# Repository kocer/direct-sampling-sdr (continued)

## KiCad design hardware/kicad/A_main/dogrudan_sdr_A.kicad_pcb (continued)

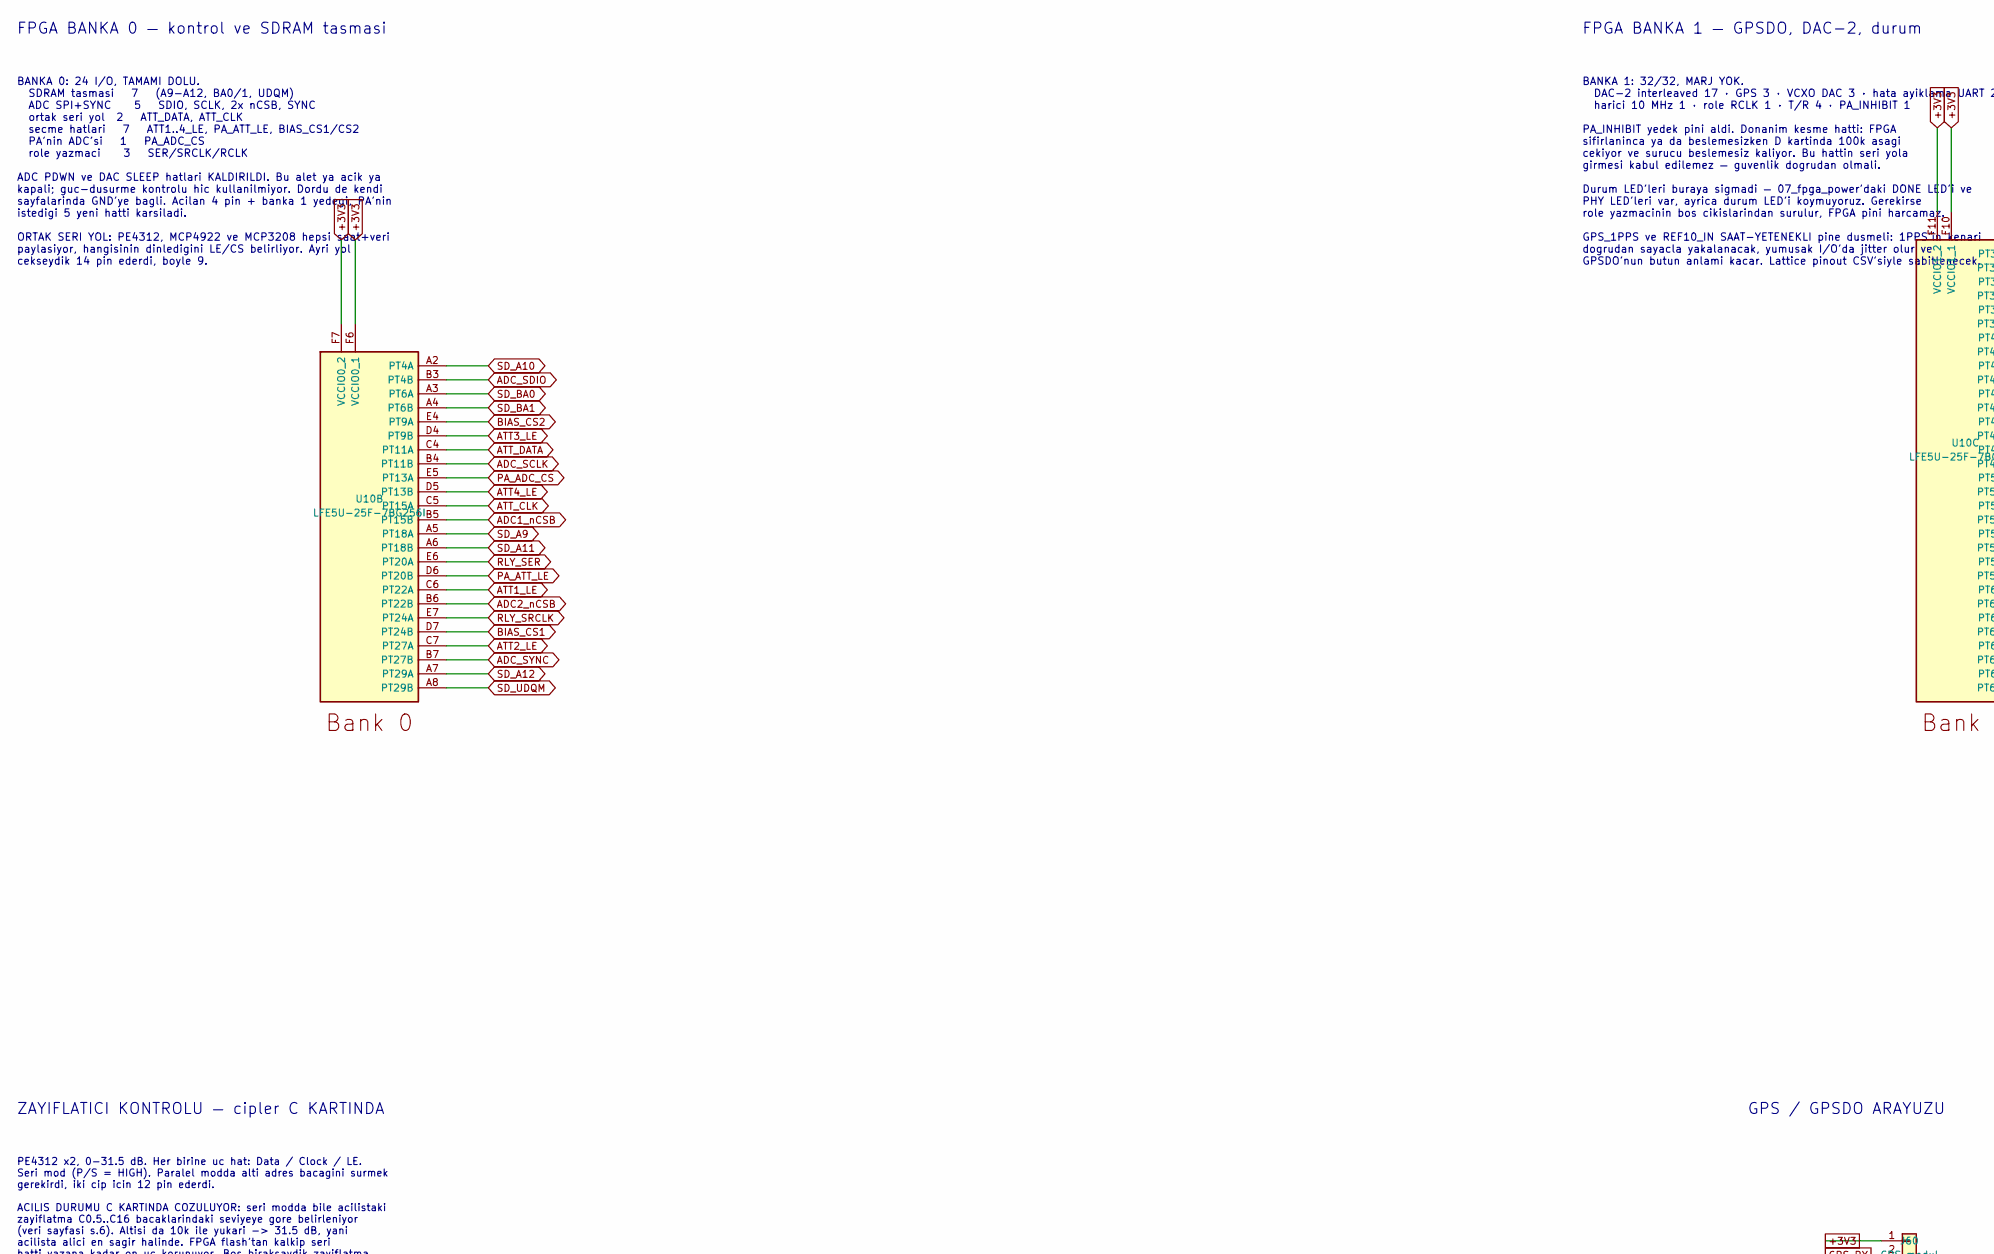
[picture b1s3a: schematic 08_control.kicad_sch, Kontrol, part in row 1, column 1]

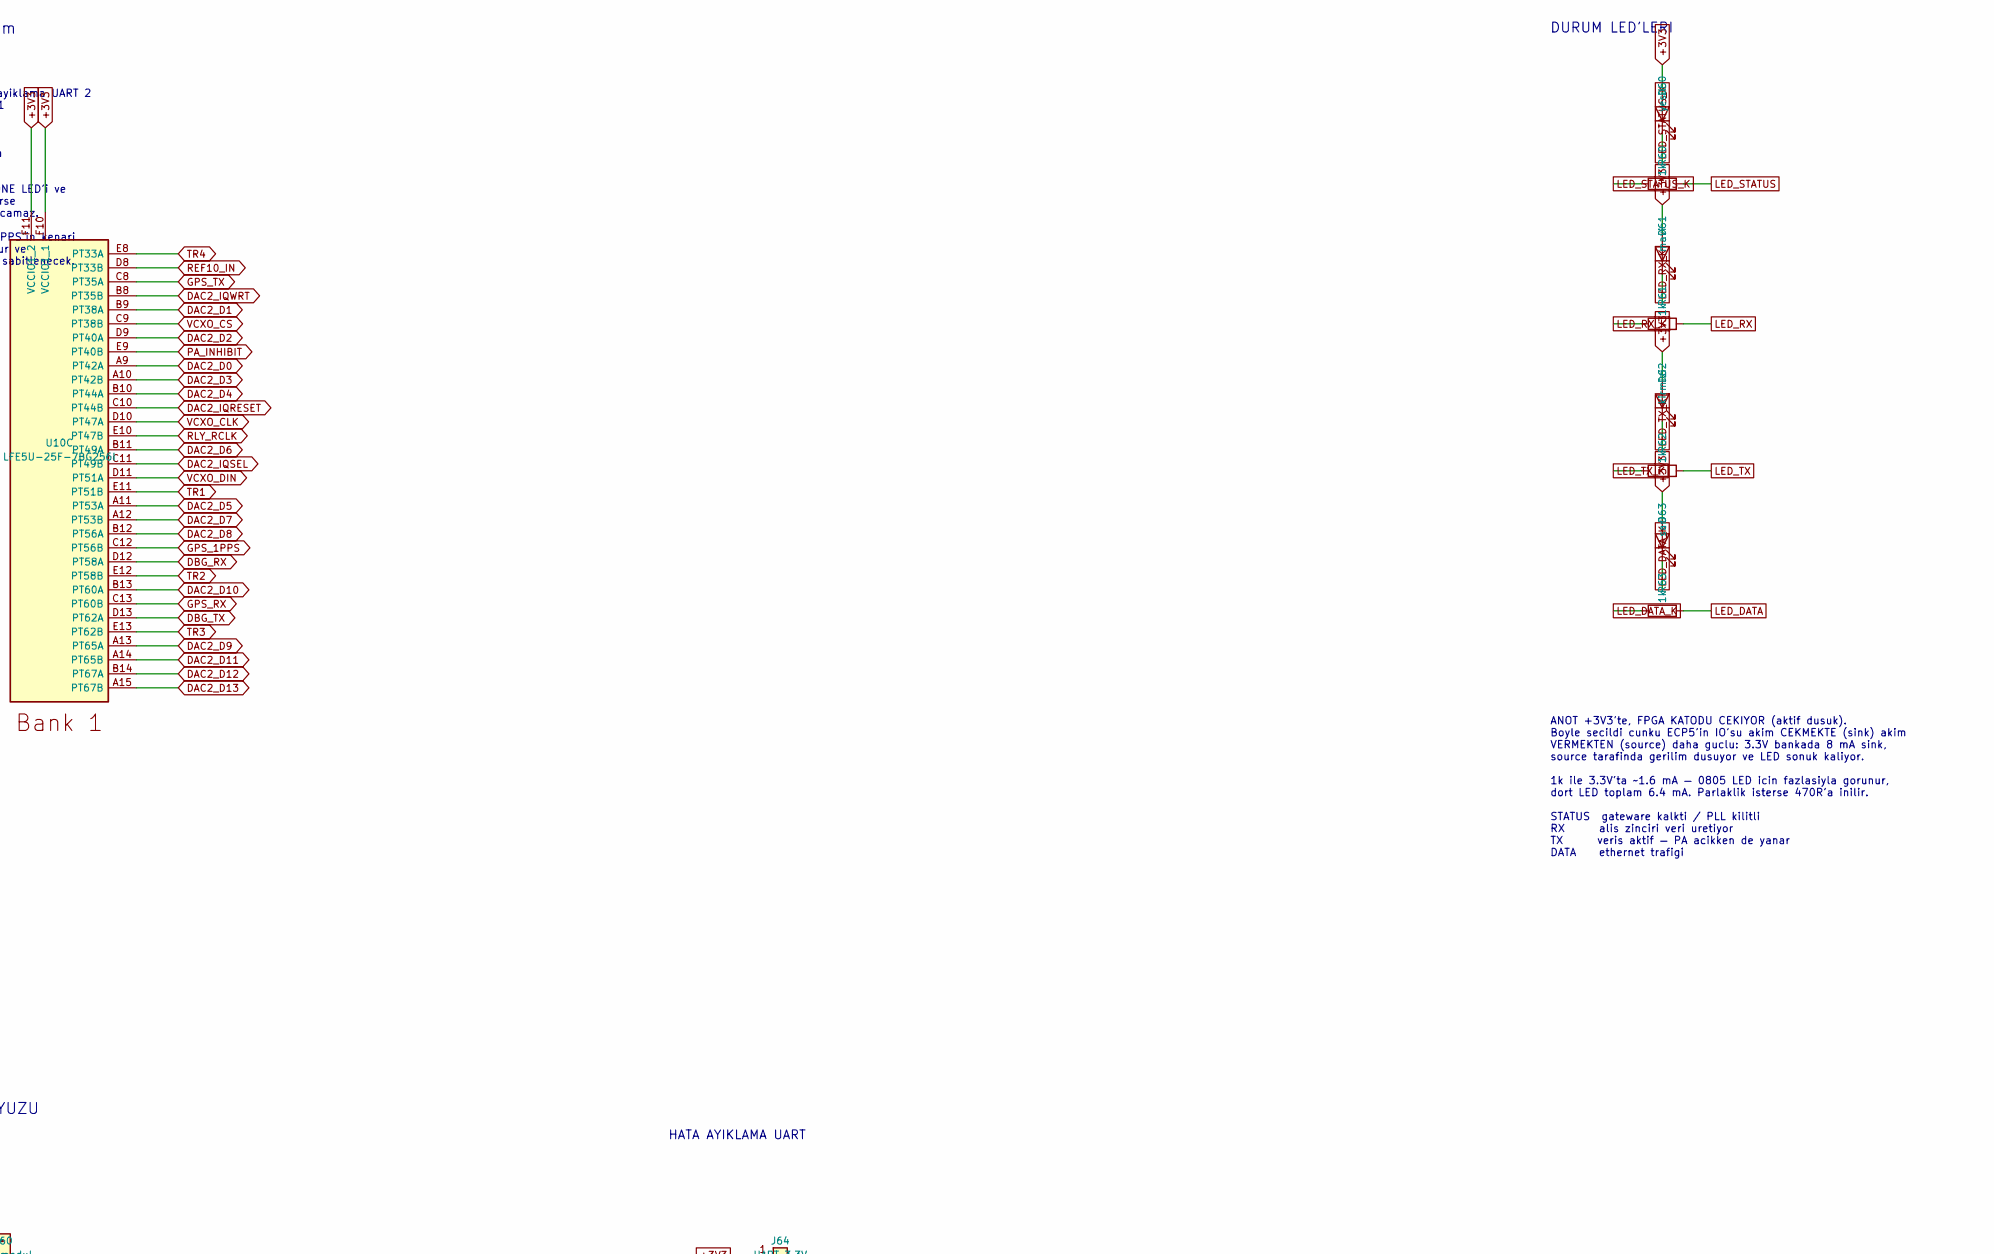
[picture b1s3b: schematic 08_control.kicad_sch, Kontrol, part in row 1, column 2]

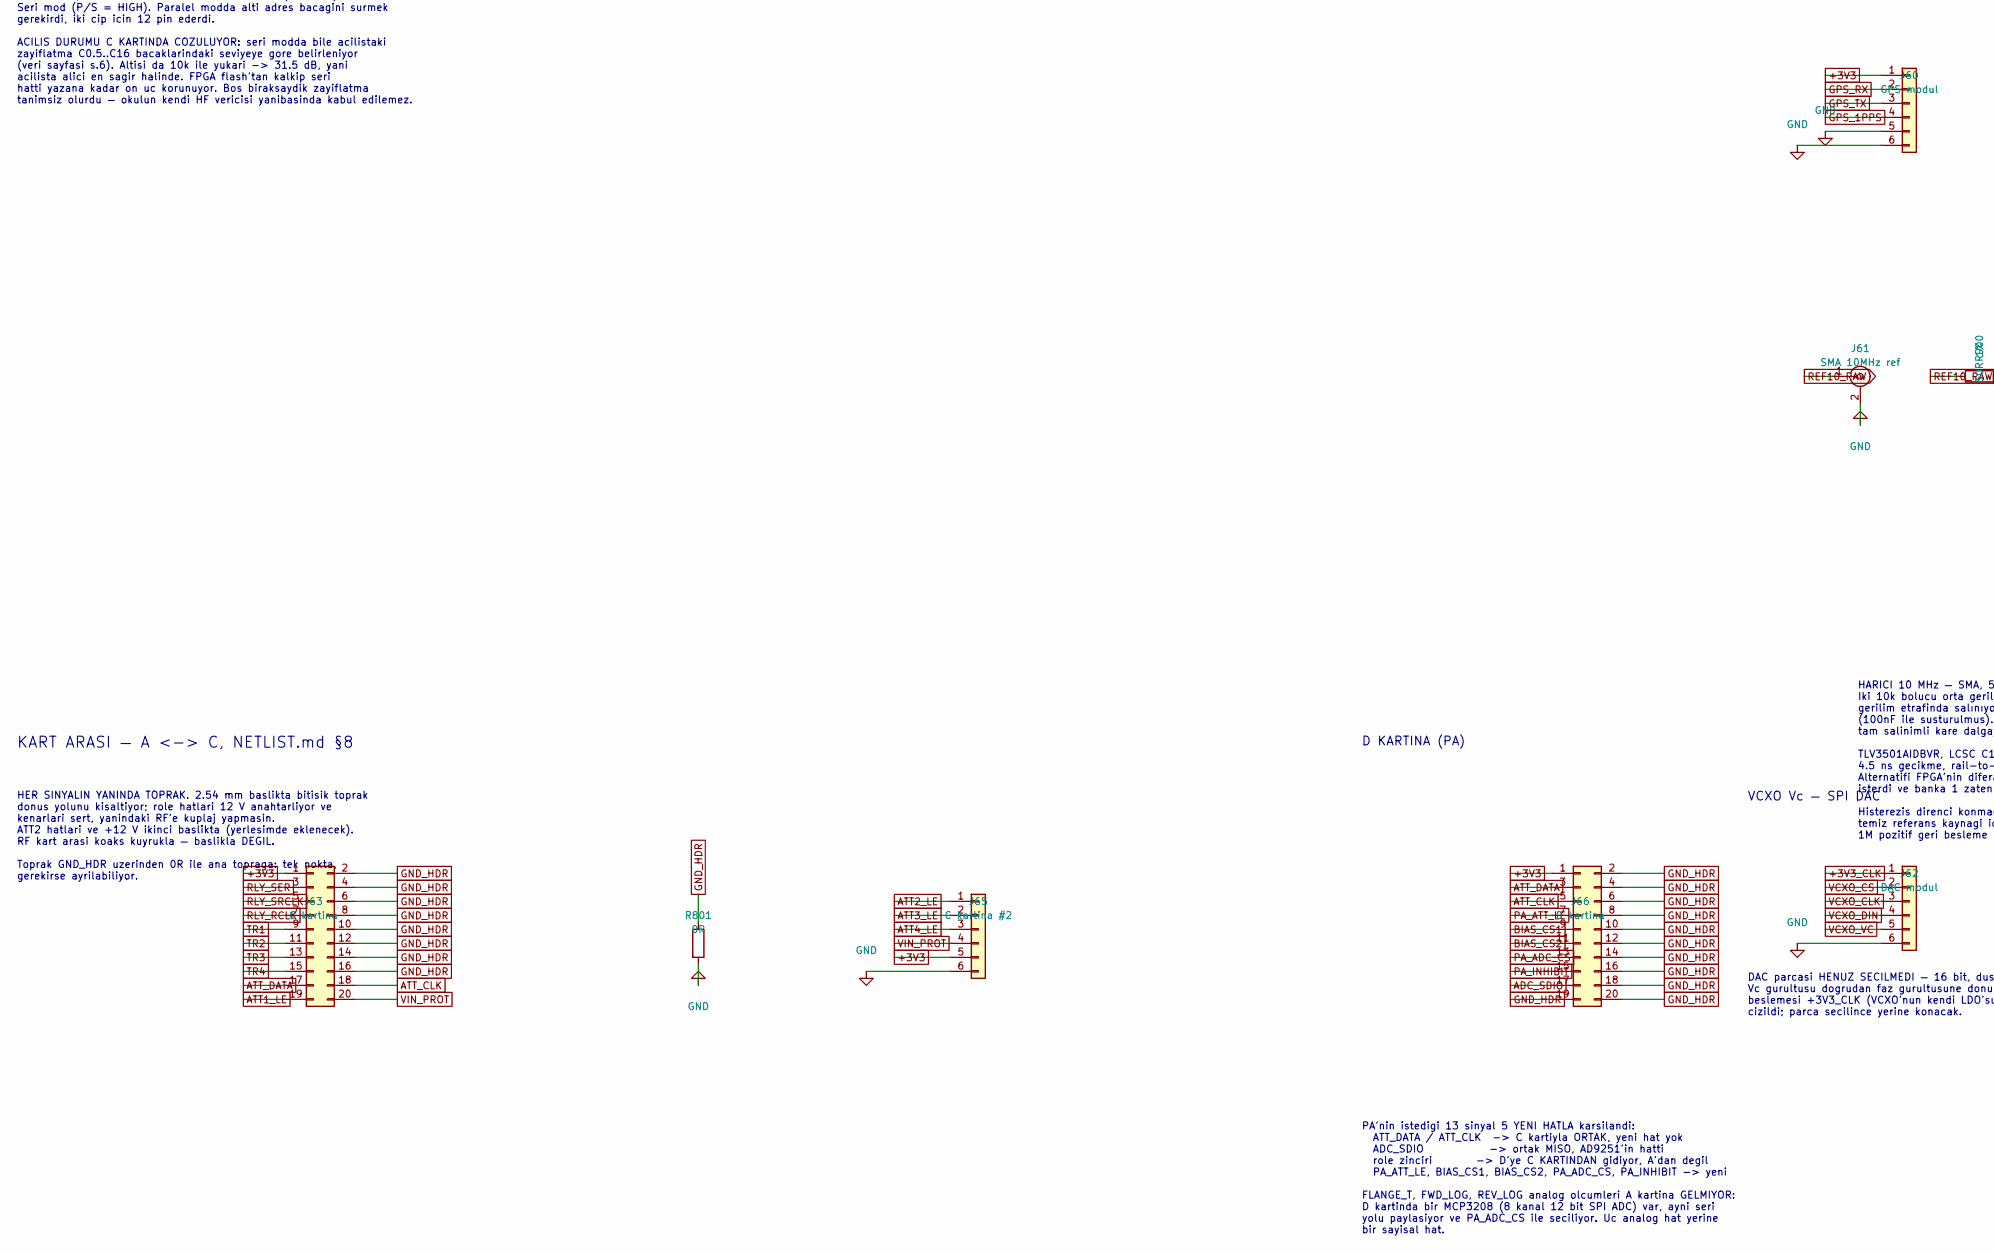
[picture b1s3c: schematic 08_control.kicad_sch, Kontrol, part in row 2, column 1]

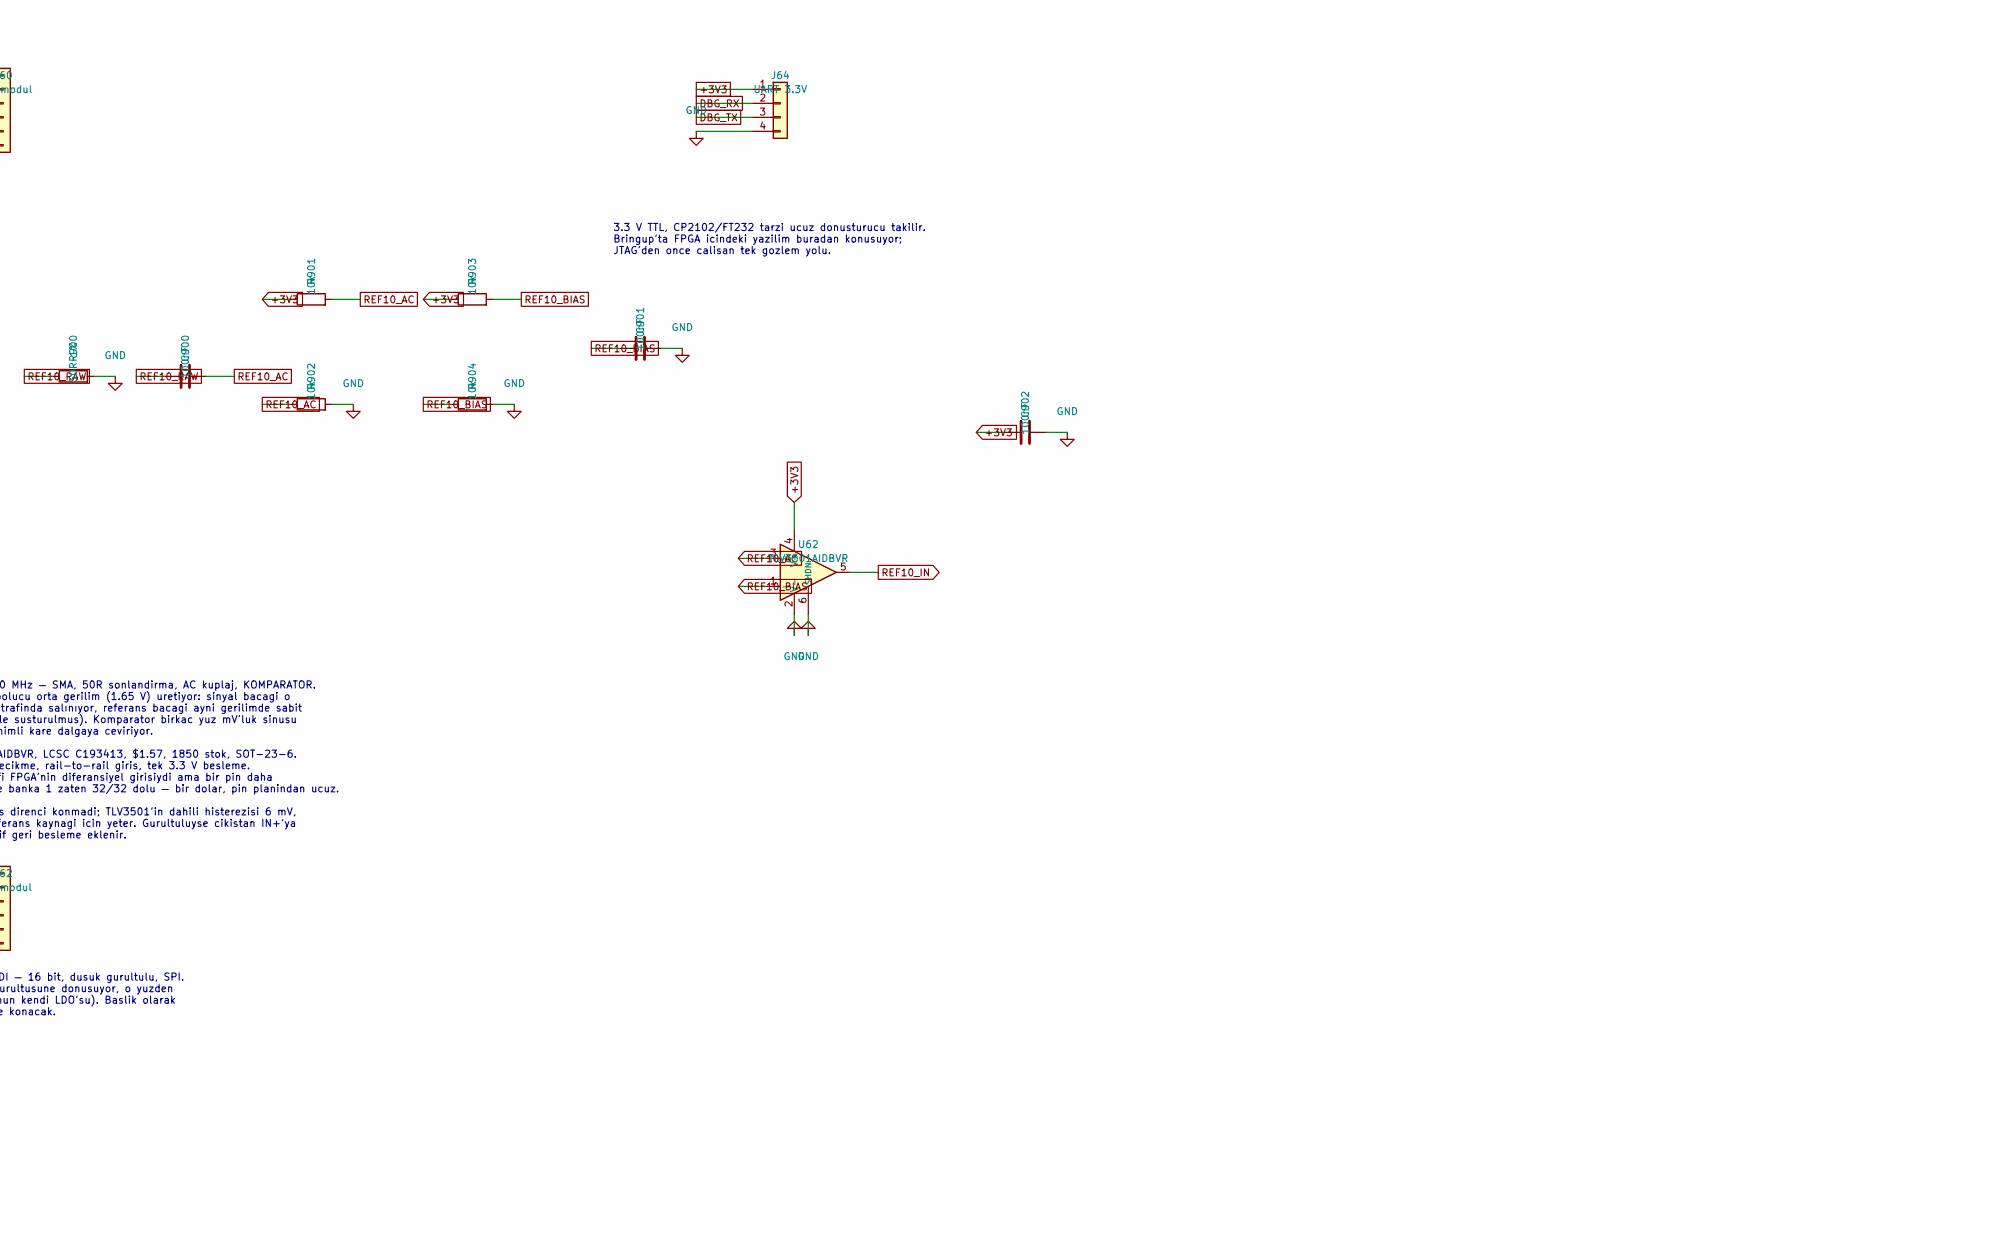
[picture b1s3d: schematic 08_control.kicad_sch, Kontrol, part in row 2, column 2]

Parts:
C900, C901, C902: 100nF; C_0603_1608Metric
D60: yesil; LED_0805_2012Metric
D61: mavi; LED_0805_2012Metric
D62: kirmizi; LED_0805_2012Metric
D63: sari; LED_0805_2012Metric
J60: GPS modul; PinHeader_1x06_P2.54mm_Vertical
J61: SMA 10MHz ref; SMA_Amphenol_132289_EdgeMount
J62: DAC modul; PinHeader_1x06_P2.54mm_Vertical
J63: C kartina; PinHeader_2x10_P2.54mm_Vertical
J64: UART 3.3V; PinHeader_1x04_P2.54mm_Vertical
J65: C kartina #2; PinHeader_1x06_P2.54mm_Vertical
J66: D kartina; PinHeader_2x10_P2.54mm_Vertical
R60, R61, R62, R63: 1k; R_0603_1608Metric
R801: 0R; R_0603_1608Metric
R900: 50R 1%; R_0603_1608Metric
R901, R902, R903, R904: 10k; R_0603_1608Metric
U10: LFE5U-25F-7BG256I; BGA-256_14.0x14.0mm_Layout16x16_P0.8mm_Ball0.45mm_Pad0.32mm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
U62: TLV3501AIDBVR; SOT-23-6

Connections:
ADC1_nCSB: U10.B5 (PT15B); also elsewhere on the board
ADC2_nCSB: U10.B6 (PT22B); also elsewhere on the board
ADC_SCLK: U10.B4 (PT11B); also elsewhere on the board
ADC_SDIO: J66.17, U10.B3 (PT4B); also elsewhere on the board
ADC_SYNC: U10.B7 (PT27B); also elsewhere on the board
ATT1_LE: J63.19, U10.C6 (PT22A)
ATT2_LE: J65.1, U10.C7 (PT27A)
ATT3_LE: J65.2, U10.D4 (PT9B)
ATT4_LE: J65.3, U10.D5 (PT13B)
ATT_CLK: J63.18, J66.5, U10.C5 (PT15A)
ATT_DATA: J63.17, J66.3, U10.C4 (PT11A)
BIAS_CS1: J66.9, U10.D7 (PT24B)
BIAS_CS2: J66.11, U10.E4 (PT9A)
DAC2_D0: U10.A9 (PT42A); also elsewhere on the board
DAC2_D1: U10.B9 (PT38A); also elsewhere on the board
DAC2_D2: U10.D9 (PT40A); also elsewhere on the board
DAC2_D3: U10.A10 (PT42B); also elsewhere on the board
DAC2_D4: U10.B10 (PT44A); also elsewhere on the board
DAC2_D5: U10.A11 (PT53A); also elsewhere on the board
DAC2_D6: U10.B11 (PT49A); also elsewhere on the board
DAC2_D7: U10.A12 (PT53B); also elsewhere on the board
DAC2_D8: U10.B12 (PT56A); also elsewhere on the board
DAC2_D9: U10.A13 (PT65A); also elsewhere on the board
DAC2_D10: U10.B13 (PT60A); also elsewhere on the board
DAC2_D11: U10.A14 (PT65B); also elsewhere on the board
DAC2_D12: U10.B14 (PT67A); also elsewhere on the board
DAC2_D13: U10.A15 (PT67B); also elsewhere on the board
DAC2_IQRESET: U10.C10 (PT44B); also elsewhere on the board
DAC2_IQSEL: U10.C11 (PT49B); also elsewhere on the board
DAC2_IQWRT: U10.B8 (PT35B); also elsewhere on the board
DBG_RX: J64.2, U10.D12 (PT58A)
DBG_TX: J64.3, U10.D13 (PT62A)
GND_HDR: J63.2, J63.4, J63.6, J63.8, J63.10, J63.12, J63.14, J63.16, J66.2, J66.4, J66.6, J66.8, J66.10, J66.12, J66.14, J66.16, J66.18, J66.19, J66.20, R801.1
GPS_1PPS: J60.4, U10.C12 (PT56B)
GPS_RX: J60.2, U10.C13 (PT60B)
GPS_TX: J60.3, U10.C8 (PT35A)
LED_DATA: R63.2; also elsewhere on the board
LED_DATA_K: D63.1 (K), R63.1
LED_RX: R61.2; also elsewhere on the board
LED_RX_K: D61.1 (K), R61.1
LED_STATUS: R60.2; also elsewhere on the board
LED_STATUS_K: D60.1 (K), R60.1
LED_TX: R62.2; also elsewhere on the board
LED_TX_K: D62.1 (K), R62.1
PA_ADC_CS: J66.13, U10.E5 (PT13A)
PA_ATT_LE: J66.7, U10.D6 (PT20B)
PA_INHIBIT: J66.15, U10.E9 (PT40B)
REF10_AC: C900.2, R901.2, R902.1, U62.3 (+)
REF10_BIAS: C901.1, R903.2, R904.1, U62.1 (-)
REF10_IN: U10.D8 (PT33B), U62.5; also elsewhere on the board
REF10_RAW: C900.1, J61.1 (In), R900.1
RLY_RCLK: J63.7, U10.E10 (PT47B)
RLY_SER: J63.3, U10.E6 (PT20A)
RLY_SRCLK: J63.5, U10.E7 (PT24A)
SD_A9: U10.A5 (PT18A); also elsewhere on the board
SD_A10: U10.A2 (PT4A); also elsewhere on the board
SD_A11: U10.A6 (PT18B); also elsewhere on the board
SD_A12: U10.A7 (PT29A); also elsewhere on the board
SD_BA0: U10.A3 (PT6A); also elsewhere on the board
SD_BA1: U10.A4 (PT6B); also elsewhere on the board
SD_UDQM: U10.A8 (PT29B); also elsewhere on the board
TR1: J63.9, U10.E11 (PT51B)
TR2: J63.11, U10.E12 (PT58B)
TR3: J63.13, U10.E13 (PT62B)
TR4: J63.15, U10.E8 (PT33A)
VCXO_CLK: J62.3, U10.D10 (PT47A)
VCXO_CS: J62.2, U10.C9 (PT38B)
VCXO_DIN: J62.4, U10.D11 (PT51A)
VCXO_VC: J62.5; also elsewhere on the board

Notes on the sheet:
FPGA BANKA 1 — GPSDO, DAC-2, durum
KART ARASI — A <-> C, NETLIST.md §8
FPGA BANKA 0 — kontrol ve SDRAM tasmasi
ANOT +3V3'te, FPGA KATODU CEKIYOR (aktif dusuk). Boyle secildi cunku ECP5'in IO'su akim CEKMEKTE (sink) akim VERMEKTEN (source) daha guclu: 3.3V bankada 8 mA sink, source tarafinda gerilim dusuyor ve LED sonuk kaliyor. 1k ile 3.3V'ta ~1.6 mA — 0805 LED icin fazlasiyla gorunur, dort LED toplam 6.4 m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
GPS / GPSDO ARAYUZU
HER SINYALIN YANINDA TOPRAK. 2.54 mm baslikta bitisik toprak donus yolunu kisaltiyor; role hatlari 12 V anahtarliyor ve kenarlari sert, yanindaki RF'e kuplaj yapmasin. ATT2 hatlari ve +12 V ikinci baslikta (yerlesimde eklenecek). RF kart arasi koaks kuyrukla — baslikla DEGIL. Toprak GND_HDR uzerind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
BANKA 0: 24 I/O, TAMAMI DOLU. SDRAM tasmasi 7 (A9-A12, BA0/1, UDQM) ADC SPI+SYNC 5 SDIO, SCLK, 2x nCSB, SYNC ortak seri yol 2 ATT_DATA, ATT_CLK secme hatlari 7 ATT1..4_LE, PA_ATT_LE, BIAS_CS1/CS2 PA'nin ADC'si 1 PA_ADC_CS role yazmaci 3 SER/SRCLK/RCLK ADC PDWN ve DAC SLEEP hatlari KALDIRILDI. Bu al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
3.3 V TTL, CP2102/FT232 tarzi ucuz donusturucu takilir. Bringup'ta FPGA icindeki yazilim buradan konusuyor; JTAG'den once calisan tek gozlem yolu.
HATA AYIKLAMA UART
PE4312 x2, 0-31.5 dB. Her birine uc hat: Data / Clock / LE. Seri mod (P/S = HIGH). Paralel modda alti adres bacagini surmek gerekirdi, iki cip icin 12 pin ederdi. ACILIS DURUMU C KARTINDA COZULUYOR: seri modda bile acilistaki zayiflatma C0.5..C16 bacaklarindaki seviyeye gore belirleniyor (veri sayf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
HARICI 10 MHz — SMA, 50R sonlandirma, AC kuplaj, KOMPARATOR. Iki 10k bolucu orta gerilim (1.65 V) uretiyor: sinyal bacagi o gerilim etrafinda salınıyor, referans bacagi ayni gerilimde sabit (100nF ile susturulmus). Komparator birkac yuz mV'luk sinusu tam salinimli kare dalgaya ceviriyor. TLV3501AID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
D KARTINA (PA)
ZAYIFLATICI KONTROLU — cipler C KARTINDA
BANKA 1: 32/32, MARJ YOK. DAC-2 interleaved 17 · GPS 3 · VCXO DAC 3 · hata ayiklama UART 2 harici 10 MHz 1 · role RCLK 1 · T/R 4 · PA_INHIBIT 1 PA_INHIBIT yedek pini aldi. Donanim kesme hatti: FPGA sifirlaninca ya da beslemesizken D kartinda 100k asagi cekiyor ve surucu beslemesiz kaliyor. Bu hatti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
PA'nin istedigi 13 sinyal 5 YENI HATLA karsilandi: ATT_DATA / ATT_CLK -> C kartiyla ORTAK, yeni hat yok ADC_SDIO -> ortak MISO, AD9251'in hatti role zinciri -> D'ye C KARTINDAN gidiyor, A'dan degil PA_ATT_LE, BIAS_CS1, BIAS_CS2, PA_ADC_CS, PA_INHIBIT -> yeni FLANGE_T, FWD_LOG, REV_LOG analog olcuml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
DAC parcasi HENUZ SECILMEDI — 16 bit, dusuk gurultulu, SPI. Vc gurultusu dogrudan faz gurultusune donusuyor, o yuzden beslemesi +3V3_CLK (VCXO'nun kendi LDO'su). Baslik olarak cizildi; parca secilince yerine konacak.
VCXO Vc — SPI DAC
DURUM LED'LERI

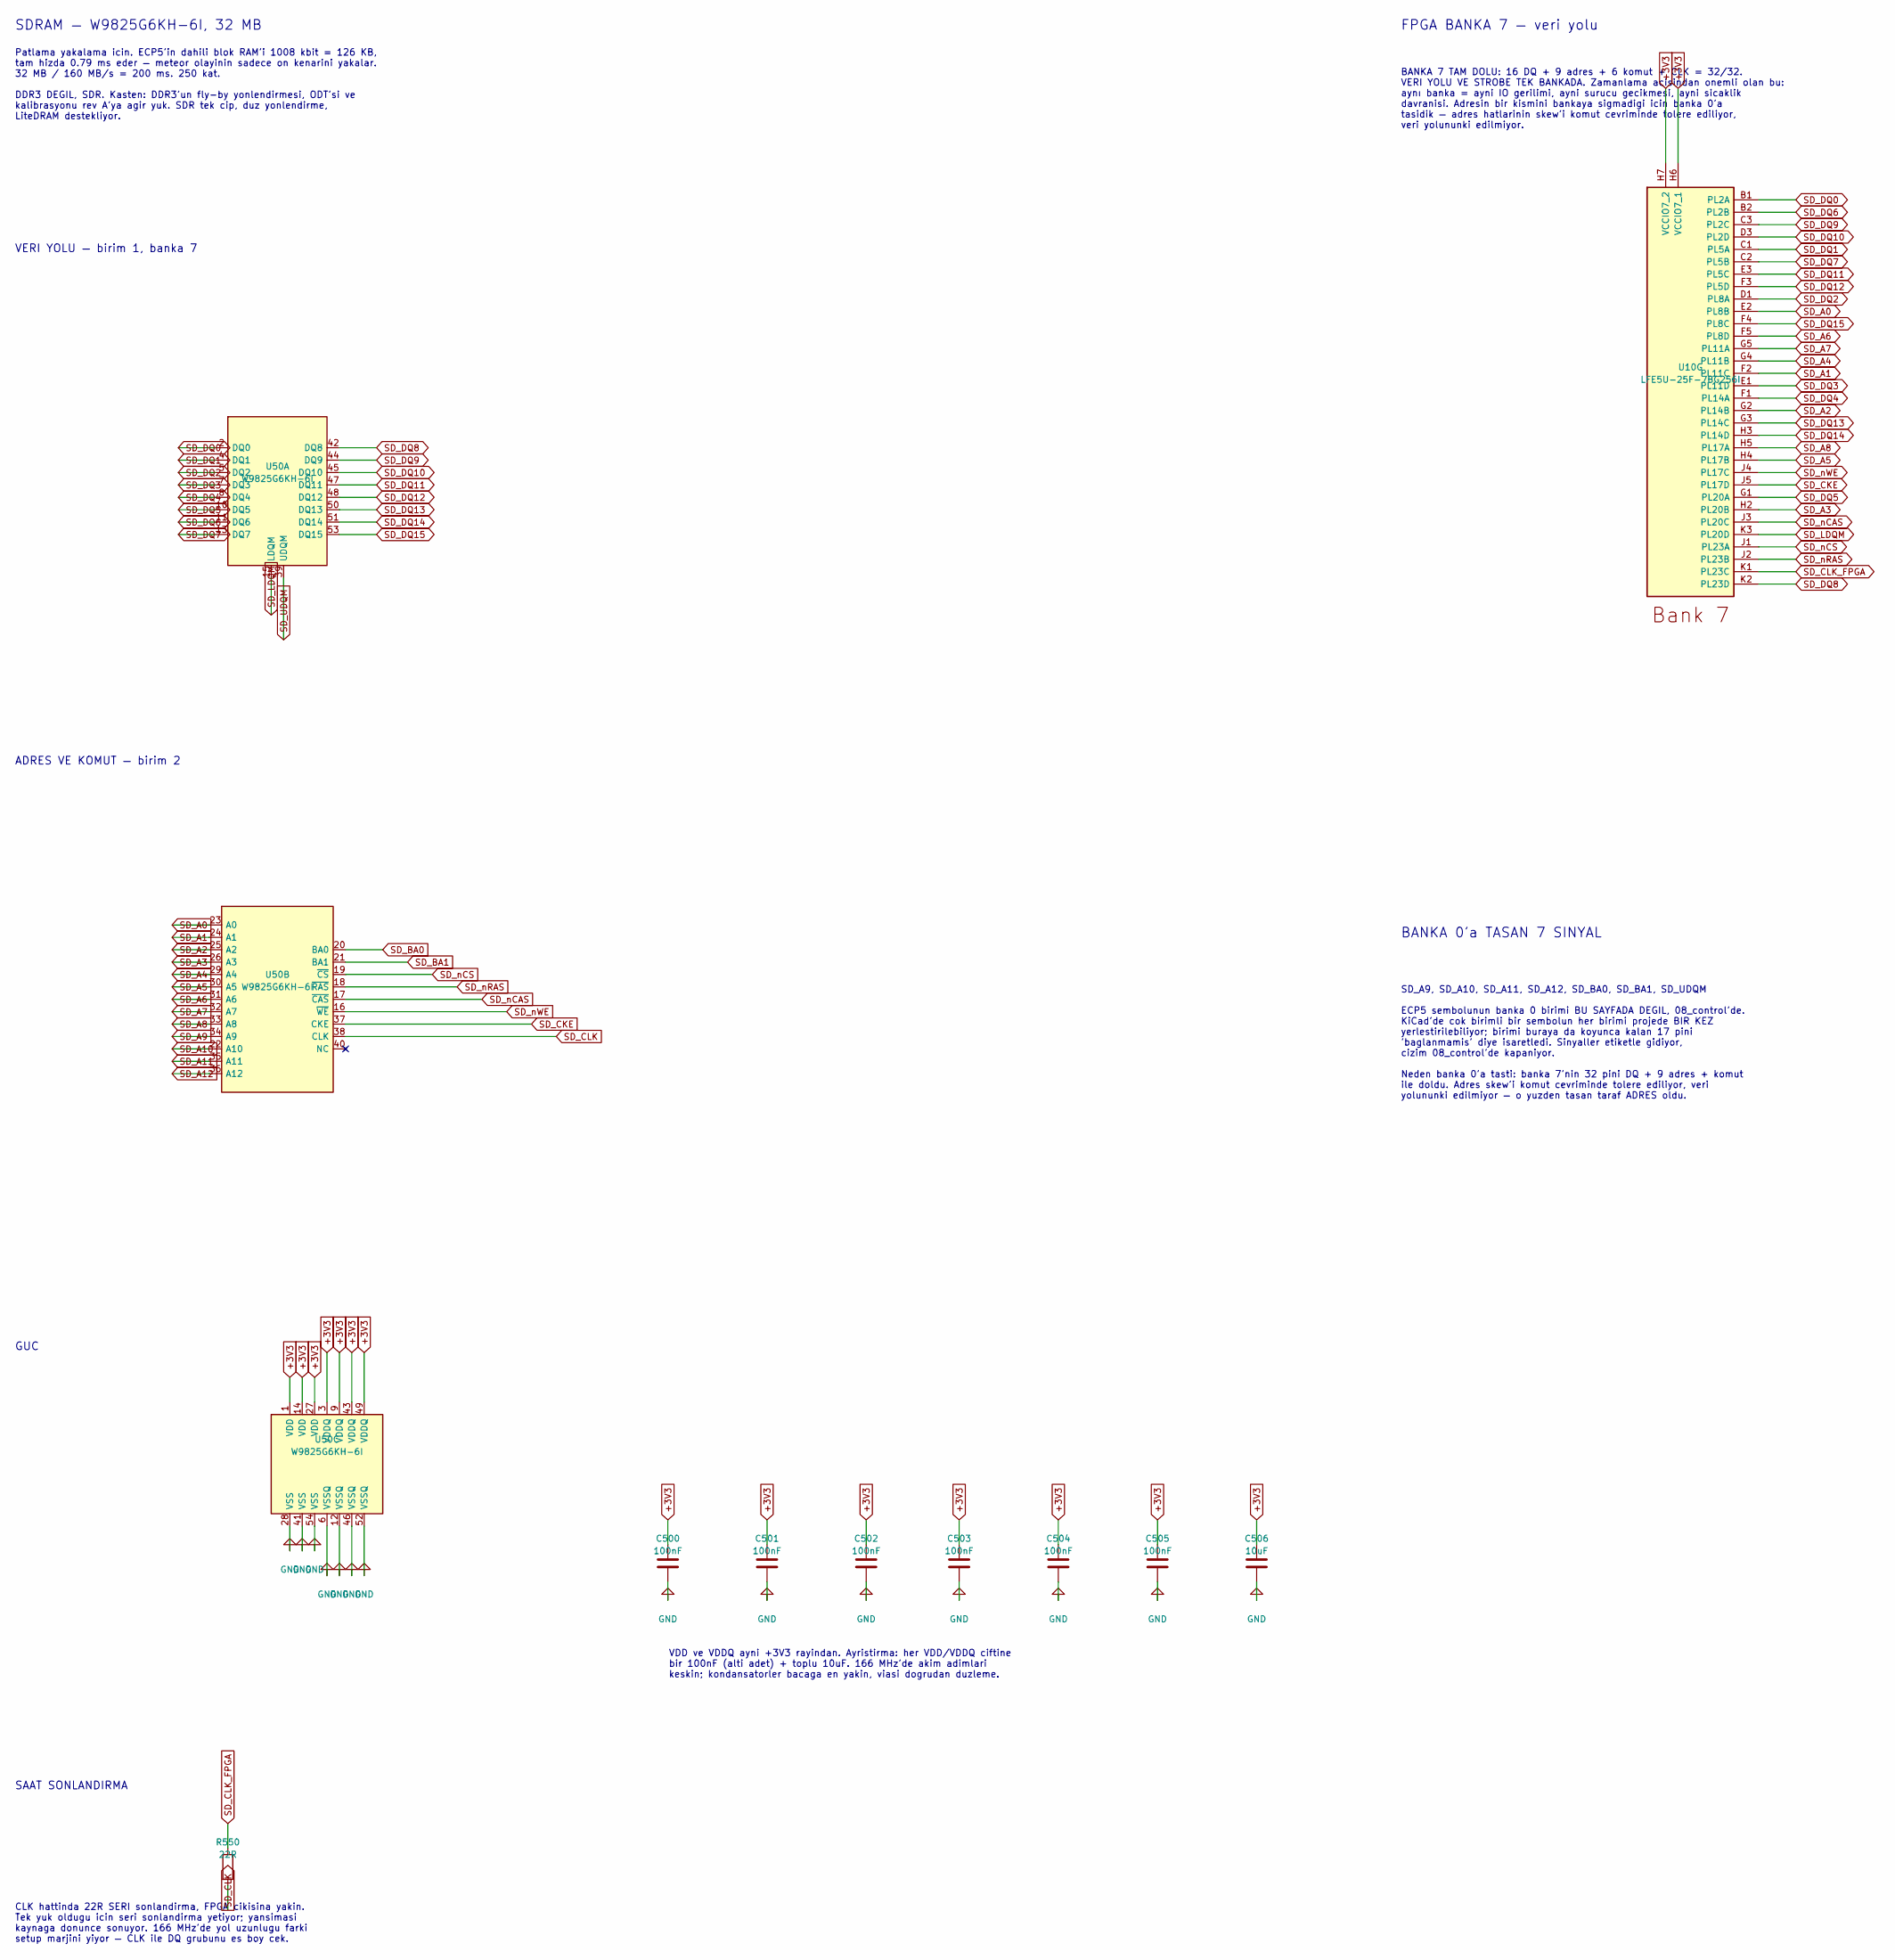
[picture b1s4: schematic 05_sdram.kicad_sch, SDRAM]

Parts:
C500, C501, C502, C503, C504, C505: 100nF; C_0603_1608Metric
C506: 10uF; C_0603_1608Metric
R550: 22R; R_0603_1608Metric
U10: LFE5U-25F-7BG256I; BGA-256_14.0x14.0mm_Layout16x16_P0.8mm_Ball0.45mm_Pad0.32mm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
U50: W9825G6KH-6I; TSOP-II-54_22.2x10.16mm_P0.8mm

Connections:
SD_A0: U10.E2 (PL8B), U50.23 (A0)
SD_A1: U10.F2 (PL11C), U50.24 (A1)
SD_A2: U10.G2 (PL14B), U50.25 (A2)
SD_A3: U10.H2 (PL20B), U50.26 (A3)
SD_A4: U10.G4 (PL11B), U50.29 (A4)
SD_A5: U10.H4 (PL17B), U50.30 (A5)
SD_A6: U10.F5 (PL8D), U50.31 (A6)
SD_A7: U10.G5 (PL11A), U50.32 (A7)
SD_A8: U10.H5 (PL17A), U50.33 (A8)
SD_A9: U50.34 (A9); also elsewhere on the board
SD_A10: U50.22 (A10); also elsewhere on the board
SD_A11: U50.35 (A11); also elsewhere on the board
SD_A12: U50.36 (A12); also elsewhere on the board
SD_BA0: U50.20 (BA0); also elsewhere on the board
SD_BA1: U50.21 (BA1); also elsewhere on the board
SD_CKE: U10.J5 (PL17D), U50.37 (CKE)
SD_CLK: R550.2, U50.38 (CLK)
SD_CLK_FPGA: R550.1, U10.K1 (PL23C)
SD_DQ0: U10.B1 (PL2A), U50.2 (DQ0)
SD_DQ1: U10.C1 (PL5A), U50.4 (DQ1)
SD_DQ2: U10.D1 (PL8A), U50.5 (DQ2)
SD_DQ3: U10.E1 (PL11D), U50.7 (DQ3)
SD_DQ4: U10.F1 (PL14A), U50.8 (DQ4)
SD_DQ5: U10.G1 (PL20A), U50.10 (DQ5)
SD_DQ6: U10.B2 (PL2B), U50.11 (DQ6)
SD_DQ7: U10.C2 (PL5B), U50.13 (DQ7)
SD_DQ8: U10.K2 (PL23D), U50.42 (DQ8)
SD_DQ9: U10.C3 (PL2C), U50.44 (DQ9)
SD_DQ10: U10.D3 (PL2D), U50.45 (DQ10)
SD_DQ11: U10.E3 (PL5C), U50.47 (DQ11)
SD_DQ12: U10.F3 (PL5D), U50.48 (DQ12)
SD_DQ13: U10.G3 (PL14C), U50.50 (DQ13)
SD_DQ14: U10.H3 (PL14D), U50.51 (DQ14)
SD_DQ15: U10.F4 (PL8C), U50.53 (DQ15)
SD_LDQM: U10.K3 (PL20D), U50.15 (LDQM)
SD_UDQM: U50.39 (UDQM); also elsewhere on the board
SD_nCAS: U10.J3 (PL20C), U50.17 (~CAS)
SD_nCS: U10.J1 (PL23A), U50.19 (~CS)
SD_nRAS: U10.J2 (PL23B), U50.18 (~RAS)
SD_nWE: U10.J4 (PL17C), U50.16 (~WE)

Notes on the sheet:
SAAT SONLANDIRMA
SDRAM — W9825G6KH-6I, 32 MB
VERI YOLU — birim 1, banka 7
ADRES VE KOMUT — birim 2
BANKA 7 TAM DOLU: 16 DQ + 9 adres + 6 komut + CLK = 32/32. VERI YOLU VE STROBE TEK BANKADA. Zamanlama acisindan onemli olan bu: aynı banka = ayni IO gerilimi, ayni surucu gecikmesi, ayni sicaklik davranisi. Adresin bir kismini bankaya sigmadigi icin banka 0'a tasidik — adres hatlarinin skew'i komut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
BANKA 0'a TASAN 7 SINYAL
VDD ve VDDQ ayni +3V3 rayindan. Ayristirma: her VDD/VDDQ ciftine bir 100nF (alti adet) + toplu 10uF. 166 MHz'de akim adimlari keskin; kondansatorler bacaga en yakin, viasi dogrudan duzleme.
SD_A9, SD_A10, SD_A11, SD_A12, SD_BA0, SD_BA1, SD_UDQM ECP5 sembolunun banka 0 birimi BU SAYFADA DEGIL, 08_control'de. KiCad'de cok birimli bir sembolun her birimi projede BIR KEZ yerlestirilebiliyor; birimi buraya da koyunca kalan 17 pini 'baglanmamis' diye isaretledi. Sinyaller etiketle gidiyor, 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
CLK hattinda 22R SERI sonlandirma, FPGA cikisina yakin. Tek yuk oldugu icin seri sonlandirma yetiyor; yansimasi kaynaga donunce sonuyor. 166 MHz'de yol uzunlugu farki setup marjini yiyor — CLK ile DQ grubunu es boy cek.
Patlama yakalama icin. ECP5'in dahili blok RAM'i 1008 kbit = 126 KB, tam hizda 0.79 ms eder — meteor olayinin sadece on kenarini yakalar. 32 MB / 160 MB/s = 200 ms. 250 kat. DDR3 DEGIL, SDR. Kasten: DDR3'un fly-by yonlendirmesi, ODT'si ve kalibrasyonu rev A'ya agir yuk. SDR tek cip, duz yonlendirme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
FPGA BANKA 7 — veri yolu
GUC
